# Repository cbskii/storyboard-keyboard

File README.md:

# Storyboard Keyboard PCB

The "Storyboard" is a 5x12 ortholinear keyboard with an E-Paper display in the middle. This is a hobby project so I've designed the keyboard with learning and experimentation in mind. Most components are SMT and can be assembled by the PCB manufacturer for added cost leaving only a few headers to be soldered by hand. The `production_files` directory contains gerber files and a BOM needed for PCB manufacturing.

## Features
- Ortholinear "split" 5x12 key arrangement.
- Hot swap key switches with split FR4 plates.
- Fits standard sized 60% keyboard cases that use a USB daughterboard (e.g. Tofu60 and Bakeneko60).
- E-Paper display for personalization. The [3.7" Waveshare e-Paper HAT](https://www.waveshare.com/3.7inch-e-paper-hat.htm) fits the best and is supported by the firmware, but the 3.52" would work as well if firmware support is added. Last set image will remain even when keyboard is unplugged/powered off (but recommended to refresh the display every now and then by rebooting the keyboard).
- USB daughterboard support (e.g. [Unified Daughterboard](https://github.com/Unified-Daughterboard/)).
- Support for different [Sparkfun Micromod](https://www.sparkfun.com/micromod) processor boards allowing for easy swap of the underlying MCU and related functionality (requires firmware change).
- QMK firmware ([development branch](https://github.com/cbskii/qmk_firmware/tree/master/keyboards/storyboard)).
- Shift register based key matrix that requires only 4 GPIOs.
- Key press interrupt support to enable lower power usage modes.

## Inspiration
- [Lumberjack](https://github.com/peej/lumberjack-keyboard)
- [Ghoul](https://github.com/tzarc/ghoul)
- [Bakeneko 60](https://github.com/kkatano/bakeneko-60)

## Pictures

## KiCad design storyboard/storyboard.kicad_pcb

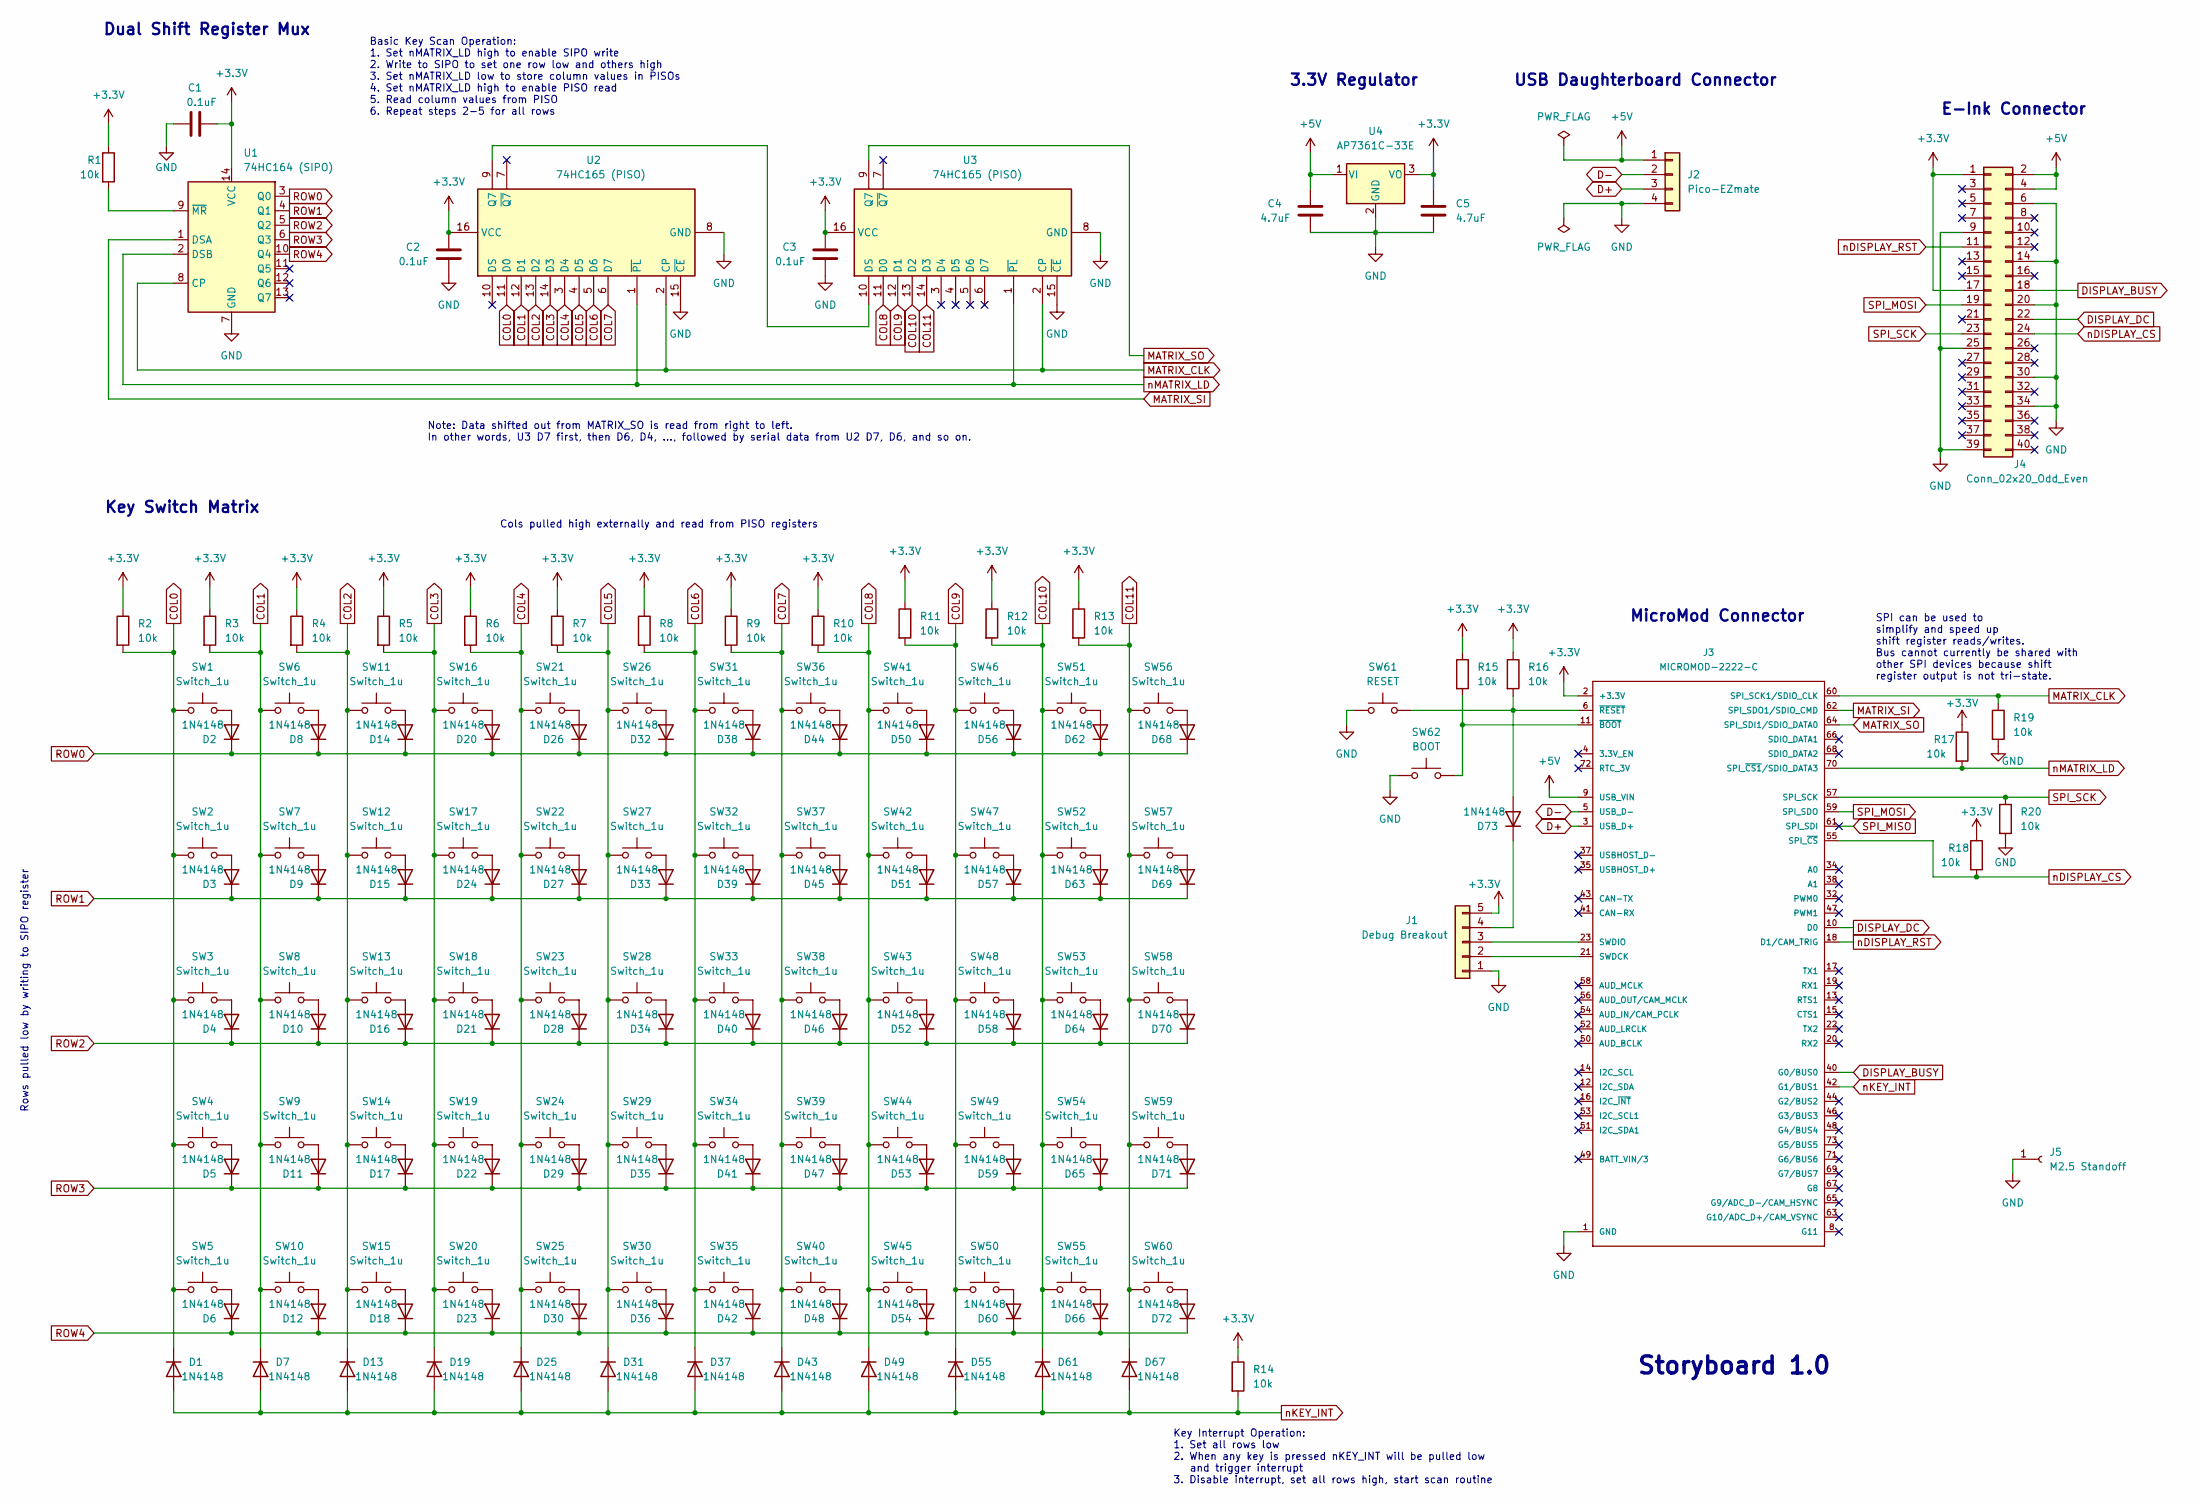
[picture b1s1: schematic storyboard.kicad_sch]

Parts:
C1, C2, C3: 0.1uF; C_0805_2012Metric
C4, C5: 4.7uF; C_0805_2012Metric
D1, D2, D3, D4, D5, D6, D7, D8, D9, D10, D11, D12, D13, D14, D15, D16, D17, D18, D19, D20, D21, D22, D23, D24, D25, D26, D27, D28, D29, D30, D31, D32, D33, D34, D35, D36, D37, D38, D39, D40, D41, D42, D43, D44, D45, D46, D47, D48, D49, D50, D51, D52, D53, D54, D55, D56, D57, D58, D59, D60, D61, D62, D63, D64, D65, D66, D67, D68, D69, D70, D71, D72, D73: 1N4148; D_SOD-523
J1: Debug Breakout; PinHeader_1x05_P2.54mm_Vertical
J2: Pico-EZmate; Pico-EZmate 4-pin
J3: MICROMOD-2222-C; SparkFun-MicroMod-M.2-CONNECTOR-E
J4: Conn_02x20_Odd_Even; Waveshare_ePaper_HAT_352
J5: M2.5 Standoff; Micromod-Standoff
R1, R2, R3, R4, R5, R6, R7, R8, R9, R10, R11, R12, R13, R14, R15, R16, R17, R18, R19, R20: 10k; R_0805_2012Metric
SW1, SW2, SW3, SW4, SW5, SW6, SW7, SW8, SW9, SW10, SW11, SW12, SW13, SW14, SW15, SW16, SW17, SW18, SW19, SW20, SW21, SW22, SW23, SW24, SW25, SW26, SW27, SW28, SW29, SW30, SW31, SW32, SW33, SW34, SW35, SW36, SW37, SW38, SW39, SW40, SW41, SW42, SW43, SW44, SW45, SW46, SW47, SW48, SW49, SW50, SW51, SW52, SW53, SW54, SW55, SW56, SW57, SW58, SW59, SW60: Switch_1u; Kailh_socket_MX
SW61: RESET; SW_PUSH_6mm
SW62: BOOT; SW_PUSH_6mm
U1: 74HC164 (SIPO); SOIC-14_3.9x8.7mm_P1.27mm
U2, U3: 74HC165 (PISO); SOIC-16_3.9x9.9mm_P1.27mm
U4: AP7361C-33E; SOT-223-3_TabPin2

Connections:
+3.3V: C1.2, C2.1, C3.1, C5.1, J1.5, J3.2 (+3.3V), J3.74 (+3.3V), J4.1, J4.17, R1.1, R2.1, R3.1, R4.1, R5.1, R6.1, R7.1, R8.1, R9.1, R10.1, R11.1, R12.1, R13.1, R14.1, R15.1, R16.1, R17.1, R18.1, U1.14 (VCC), U2.16 (VCC), U3.16 (VCC), U4.3 (VO)
+5V: C4.1, J2.1, J3.9 (USB_VIN), J4.2, J4.4, U4.1 (VI)
COL0: D1.1 (K), R2.2, SW1.1, SW2.1, SW3.1, SW4.1, SW5.1, U2.11 (D0)
COL1: D7.1 (K), R3.2, SW6.1, SW7.1, SW8.1, SW9.1, SW10.1, U2.12 (D1)
COL2: D13.1 (K), R4.2, SW11.1, SW12.1, SW13.1, SW14.1, SW15.1, U2.13 (D2)
COL3: D19.1 (K), R5.2, SW16.1, SW17.1, SW18.1, SW19.1, SW20.1, U2.14 (D3)
COL4: D25.1 (K), R6.2, SW21.1, SW22.1, SW23.1, SW24.1, SW25.1, U2.3 (D4)
COL5: D31.1 (K), R7.2, SW26.1, SW27.1, SW28.1, SW29.1, SW30.1, U2.4 (D5)
COL6: D37.1 (K), R8.2, SW31.1, SW32.1, SW33.1, SW34.1, SW35.1, U2.5 (D6)
COL7: D43.1 (K), R9.2, SW36.1, SW37.1, SW38.1, SW39.1, SW40.1, U2.6 (D7)
COL8: D49.1 (K), R10.2, SW41.1, SW42.1, SW43.1, SW44.1, SW45.1, U3.11 (D0)
COL9: D55.1 (K), R11.2, SW46.1, SW47.1, SW48.1, SW49.1, SW50.1, U3.12 (D1)
COL10: D61.1 (K), R12.2, SW51.1, SW52.1, SW53.1, SW54.1, SW55.1, U3.13 (D2)
COL11: D67.1 (K), R13.2, SW56.1, SW57.1, SW58.1, SW59.1, SW60.1, U3.14 (D3)
D+: J2.3, J3.3 (USB_D+)
D-: J2.2, J3.5 (USB_D-)
DISPLAY_BUSY: J3.40 (G0/BUS0), J4.18
DISPLAY_DC: J3.10 (D0), J4.22
GND: C1.1, C2.2, C3.2, C4.2, C5.2, J1.1, J2.4, J3.1 (GND), J3.7 (GND), J3.33 (GND), J3.36 (GND), J3.39 (GND), J3.45 (GND), J3.75 (GND), J4.6, J4.9, J4.14, J4.20, J4.25, J4.30, J4.34, J4.39, J5.1, R19.2, R20.2, SW61.1, SW62.1, U1.7 (GND), U2.8 (GND), U2.15 (~CE), U3.8 (GND), U3.15 (~CE), U4.2 (GND)
MATRIX_CLK: J3.60 (SPI_SCK1/SDIO_CLK), R19.1, U1.8 (CP), U2.2 (CP), U3.2 (CP)
MATRIX_SI: J3.62 (SPI_SDO1/SDIO_CMD), U1.1 (DSA)
MATRIX_SO: J3.64 (SPI_SDI1/SDIO_DATA0), U3.9 (Q7)
unnamed: D2.2 (A), SW1.2
unnamed: D3.2 (A), SW2.2
unnamed: D4.2 (A), SW3.2
unnamed: D5.2 (A), SW4.2
unnamed: D6.2 (A), SW5.2
unnamed: D8.2 (A), SW6.2
unnamed: D9.2 (A), SW7.2
unnamed: D10.2 (A), SW8.2
unnamed: D11.2 (A), SW9.2
unnamed: D12.2 (A), SW10.2
unnamed: D14.2 (A), SW11.2
unnamed: D15.2 (A), SW12.2
unnamed: D16.2 (A), SW13.2
unnamed: D17.2 (A), SW14.2
unnamed: D18.2 (A), SW15.2
unnamed: D20.2 (A), SW16.2
unnamed: D21.2 (A), SW18.2
unnamed: D22.2 (A), SW19.2
unnamed: D23.2 (A), SW20.2
unnamed: D24.2 (A), SW17.2
unnamed: D26.2 (A), SW21.2
unnamed: D27.2 (A), SW22.2
unnamed: D28.2 (A), SW23.2
unnamed: D29.2 (A), SW24.2
unnamed: D30.2 (A), SW25.2
unnamed: D32.2 (A), SW26.2
unnamed: D33.2 (A), SW27.2
unnamed: D34.2 (A), SW28.2
unnamed: D35.2 (A), SW29.2
unnamed: D36.2 (A), SW30.2
unnamed: D38.2 (A), SW31.2
unnamed: D39.2 (A), SW32.2
unnamed: D40.2 (A), SW33.2
unnamed: D41.2 (A), SW34.2
unnamed: D42.2 (A), SW35.2
unnamed: D44.2 (A), SW36.2
unnamed: D45.2 (A), SW37.2
unnamed: D46.2 (A), SW38.2
unnamed: D47.2 (A), SW39.2
unnamed: D48.2 (A), SW40.2
unnamed: D50.2 (A), SW41.2
unnamed: D51.2 (A), SW42.2
unnamed: D52.2 (A), SW43.2
unnamed: D53.2 (A), SW44.2
unnamed: D54.2 (A), SW45.2
unnamed: D56.2 (A), SW46.2
unnamed: D57.2 (A), SW47.2
unnamed: D58.2 (A), SW48.2
unnamed: D59.2 (A), SW49.2
unnamed: D60.2 (A), SW50.2
unnamed: D62.2 (A), SW51.2
unnamed: D63.2 (A), SW52.2
unnamed: D64.2 (A), SW53.2
unnamed: D65.2 (A), SW54.2
unnamed: D66.2 (A), SW55.2
unnamed: D68.2 (A), SW56.2
unnamed: D69.2 (A), SW57.2
unnamed: D70.2 (A), SW58.2
unnamed: D71.2 (A), SW59.2
unnamed: D72.2 (A), SW60.2
unnamed: D73.1 (K), J1.4
unnamed: D73.2 (A), J3.6 (~RESET), R16.2, SW61.2
unnamed: J1.2, J3.21 (SWDCK)
unnamed: J1.3, J3.23 (SWDIO)
unnamed: J3.11 (~BOOT), R15.2, SW62.2
unnamed: R1.2, U1.9 (~MR)
unnamed: U2.9 (Q7), U3.10 (DS)
ROW0: D2.1 (K), D8.1 (K), D14.1 (K), D20.1 (K), D26.1 (K), D32.1 (K), D38.1 (K), D44.1 (K), D50.1 (K), D56.1 (K), D62.1 (K), D68.1 (K), U1.3 (Q0)
ROW1: D3.1 (K), D9.1 (K), D15.1 (K), D24.1 (K), D27.1 (K), D33.1 (K), D39.1 (K), D45.1 (K), D51.1 (K), D57.1 (K), D63.1 (K), D69.1 (K), U1.4 (Q1)
ROW2: D4.1 (K), D10.1 (K), D16.1 (K), D21.1 (K), D28.1 (K), D34.1 (K), D40.1 (K), D46.1 (K), D52.1 (K), D58.1 (K), D64.1 (K), D70.1 (K), U1.5 (Q2)
ROW3: D5.1 (K), D11.1 (K), D17.1 (K), D22.1 (K), D29.1 (K), D35.1 (K), D41.1 (K), D47.1 (K), D53.1 (K), D59.1 (K), D65.1 (K), D71.1 (K), U1.6 (Q3)
ROW4: D6.1 (K), D12.1 (K), D18.1 (K), D23.1 (K), D30.1 (K), D36.1 (K), D42.1 (K), D48.1 (K), D54.1 (K), D60.1 (K), D66.1 (K), D72.1 (K), U1.10 (Q4)
SPI_MISO: J3.61 (SPI_SDI)
SPI_MOSI: J3.59 (SPI_SDO), J4.19
SPI_SCK: J3.57 (SPI_SCK), J4.23, R20.1
nDISPLAY_CS: J3.55 (SPI_~CS), J4.24, R18.2
nDISPLAY_RST: J3.18 (D1/CAM_TRIG), J4.11
nKEY_INT: D1.2 (A), D7.2 (A), D13.2 (A), D19.2 (A), D25.2 (A), D31.2 (A), D37.2 (A), D43.2 (A), D49.2 (A), D55.2 (A), D61.2 (A), D67.2 (A), J3.42 (G1/BUS1), R14.2
nMATRIX_LD: J3.70 (SPI_~CS1/SDIO_DATA3), R17.2, U1.2 (DSB), U2.1 (~PL), U3.1 (~PL)

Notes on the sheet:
E-Ink Connector
USB Daughterboard Connector
Key Interrupt Operation: 1. Set all rows low 2. When any key is pressed nKEY_INT will be pulled low and trigger interrupt 3. Disable interrupt, set all rows high, start scan routine
Note: Data shifted out from MATRIX_SO is read from right to left. In other words, U3 D7 first, then D6, D4, ..., followed by serial data from U2 D7, D6, and so on.
Storyboard 1.0
3.3V Regulator
SPI can be used to simplify and speed up shift register reads/writes. Bus cannot currently be shared with other SPI devices because shift register output is not tri-state.
Cols pulled high externally and read from PISO registers
Key Switch Matrix
Rows pulled low by writing to SIPO register
MicroMod Connector
Dual Shift Register Mux
Basic Key Scan Operation: 1. Set nMATRIX_LD high to enable SIPO write 2. Write to SIPO to set one row low and others high 3. Set nMATRIX_LD low to store column values in PISOs 4. Set nMATRIX_LD high to enable PISO read 5. Read column values from PISO 6. Repeat steps 2-5 for all rows

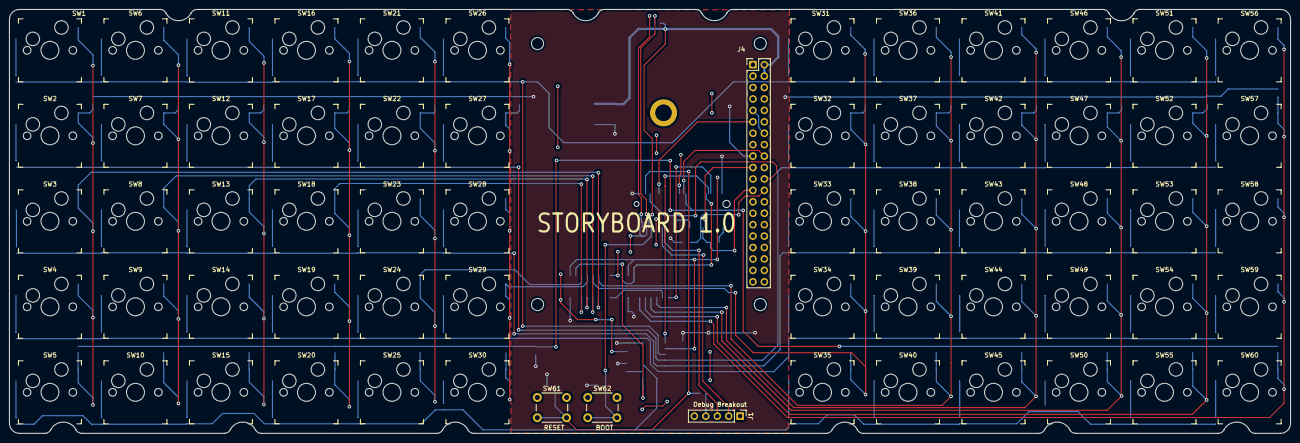
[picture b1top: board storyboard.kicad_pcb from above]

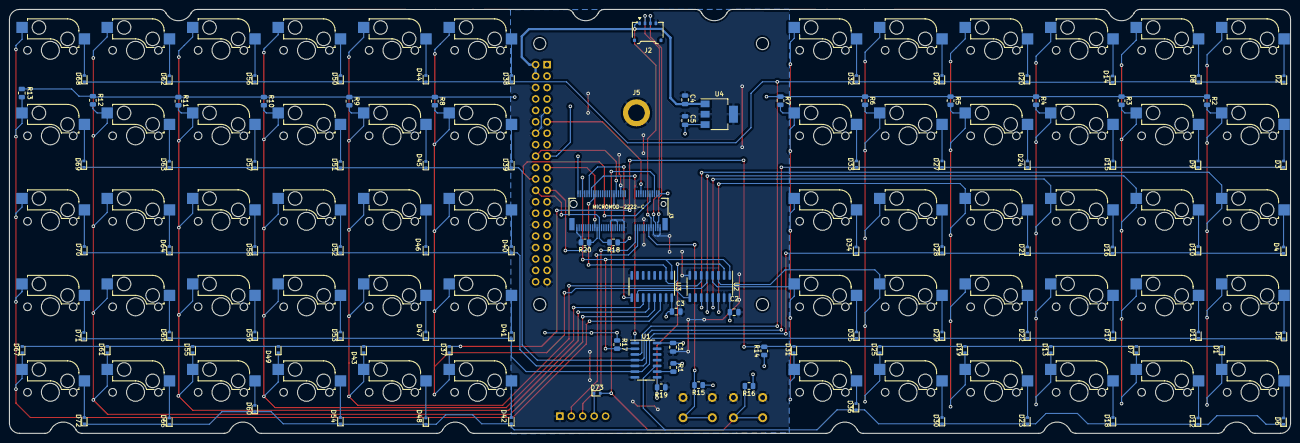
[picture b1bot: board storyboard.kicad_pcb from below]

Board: 2 copper layers, 284.7 x 94.2 mm, 169 parts (105 on the bottom side), 100 nets.

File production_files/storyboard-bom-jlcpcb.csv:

Comment,Designator,Footprint,JLCPCB Part #,SMD Assembly
Kailh_socket_MX,"SW51,SW16,SW9,SW35,SW28,SW19,SW38,SW11,SW15,SW47,SW17,SW23,SW41,SW13,SW44,SW45,SW56,SW8,SW59,SW34,SW26,SW36,SW25,SW50,SW54,SW53,SW37,SW18,SW4,SW46,SW33,SW14,SW52,SW3,SW58,SW40,SW43,SW55,SW12,SW6,SW21,SW48,SW32,SW5,SW39,SW49,SW20,SW7,SW29,SW57,SW10,SW42,SW27,SW24,SW60,SW30,SW31,SW1,SW22,SW2",Kailh_socket_MX,C5156480,Yes
AP7361C-33E,U4,SOT-223-3_TabPin2,C500795,Yes
10k,"R11,R6,R16,R14,R20,R12,R18,R1,R19,R8,R13,R17,R15,R5,R7,R10,R9,R3,R4,R2",R_0805_2012Metric,C2930231,Yes
1N4148,"D8,D35,D56,D21,D9,D33,D57,D7,D34,D62,D36,D15,D11,D17,D29,D39,D49,D40,D63,D59,D24,D32,D12,D20,D42,D38,D46,D4,D45,D47,D28,D54,D61,D50,D58,D22,D66,D13,D68,D72,D41,D44,D69,D70,D65,D6,D10,D31,D67,D73,D3,D18,D16,D23,D2,D30,D25,D1,D60,D5,D26,D51,D27,D55,D71,D52,D64,D37,D43,D53,D14,D48,D19",D_SOD-523,C727112,Yes
74HC165 ,"U3,U2",SOIC-16_3.9x9.9mm_P1.27mm,C5613,Yes
CONN HEADER SMD 4POS 1.2MM,J2,CONN HEADER SMD 4POS 1.2MM,C588524,Yes
74HC164 ,U1,SOIC-14_3.9x8.7mm_P1.27mm,C5419,Yes
4.7uF,"C4,C5",C_0805_2012Metric,C98192,Yes
0.1uF,"C3,C2,C1",C_0805_2012Metric,C126469,Yes
CONN M.2 FMALE 67POS 0.020 GOLD,J3,M.2-CONNECTOR-E,C2977809,Yes
BOOT Switch,SW62,SW_PUSH_6mm,,No
RESET Switch,SW61,SW_PUSH_6mm,,No
Debug Breakout,J1,PinHeader_1x05_P2.54mm_Vertical,,No
Conn_02x20_Odd_Even,J4,Waveshare_ePaper_HAT_352,,No
M2.5 Standoff,J5,Micromod-Standoff,,No

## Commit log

2023-07-28 Initial project upload
    PCB and schematic have not been fully tested. Not ready for manufacture.
2023-07-28 Move versions.txt to root
2023-07-28 resolve schematic parity issues
2023-07-28 minor change to test commit
2023-07-29 add 3d step files for remaining foot prints
2023-07-29 move production files (gerbers) to root
2023-07-30 moved all SMD components to bottom for cheaper assembly
2023-10-04 update latest production files
2023-10-04 add missing BOM and assembly files
2023-10-04 add key scan notes to schematic
2023-10-04 Add display info to README
2023-10-17 Add QMK firmware to readme
2023-11-27 Add support for Tofu 60 2.0 case.
    Changes:
    1. Modify original split plate to show copper border around edges.
    2. Add support for Tofu60 2.0 top mount with a new 60% plate
    specifically designed for the Storyboard.
    3. Add gerbers for new plate and update production_files directory.
2023-12-15 Update README.md with 3.7" pictures
